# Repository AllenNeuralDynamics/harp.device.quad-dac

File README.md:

# harp.device.quad-dac
This repository contains the hardware, firmware, and software related to the Harp quad DAC

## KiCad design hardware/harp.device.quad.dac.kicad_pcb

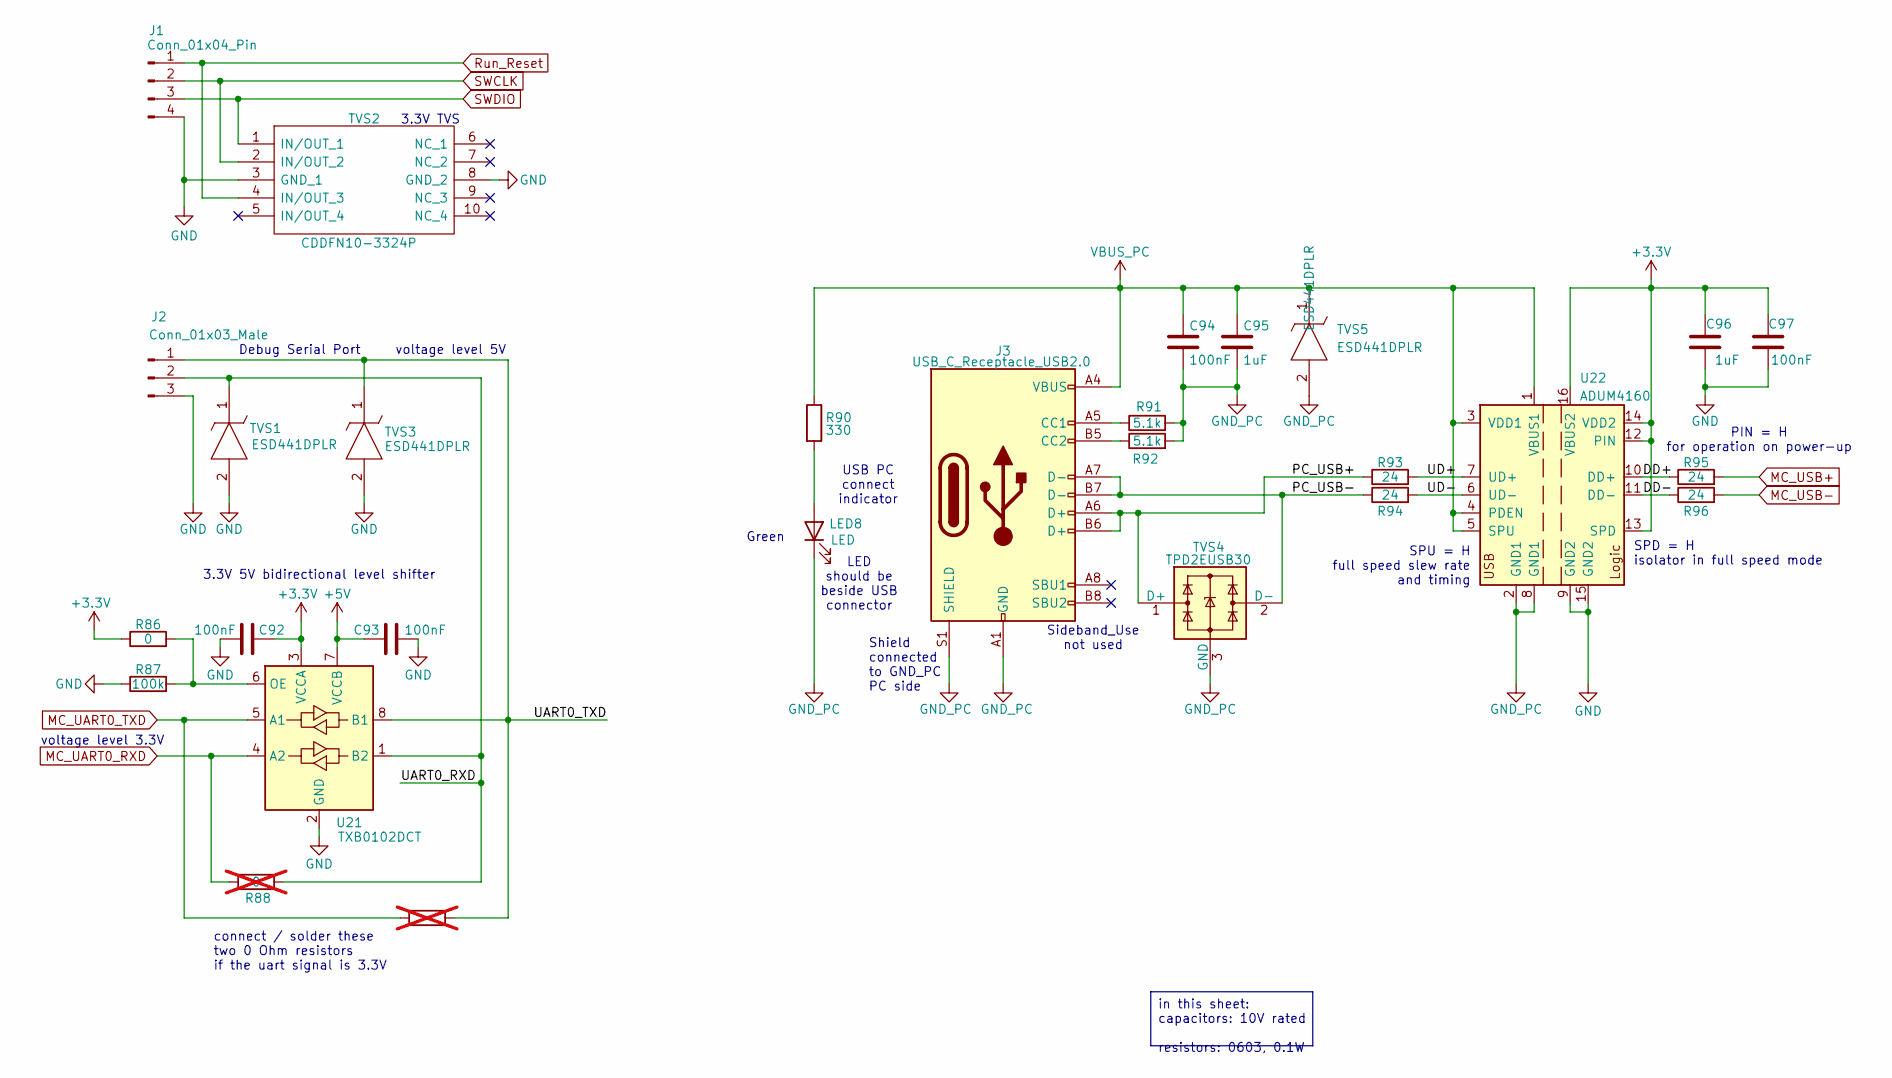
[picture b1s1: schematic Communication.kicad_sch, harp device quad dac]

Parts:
C92, C93, C94, C97: 100nF; C_0603_1608Metric; Rated Voltage 50V; Tolerance 10%; Manufacturer_Part_Number C0603C104K5RACTU
C95, C96: 1uF; C_0603_1608Metric; Rated Voltage 50V; Tolerance 10%; Manufacturer_Part_Number C1608X7R1H105K080AB
J1: Conn_01x04_Pin; PinHeader_1x04_P2.54mm_Vertical; Manufacturer_Part_Number n/a
J2: Conn_01x03_Male; PinHeader_1x03_P2.54mm_Vertical; Manufacturer_Part_Number n/a
J3: USB_C_Receptacle_USB2.0; USB_C_Receptacle_JAE_DX07S016JA1R1500; Manufacturer_Part_Number DX07S016JA1R1500
LED8: LED; LED_0603_1608Metric_Pad1.05x0.95mm_HandSolder; MPN XZCDGK53W-1VF
R86: 0; R_0603_1608Metric; MPN RC0603JR-070RL
R87: 100k; R_0603_1608Metric; Tolerance 1%; MPN RC0603FR-07100KL
R88, R89: 0; R_0603_1608Metric; MPN RC0603JR-070RL; not fitted
R90: 330; R_0603_1608Metric; Tolerance 1%; MPN RC0603FR-07330RL
R91, R92: 5.1k; R_0603_1608Metric; Tolerance 1%; MPN RC0603FR-075K1L
R93, R94, R95, R96: 24; R_0603_1608Metric; Tolerance 1%; MPN AC0603FR-0724RL
TVS1, TVS3, TVS5: ESD441DPLR; Manufacturer_Part_Number ESD441DPLR; Mouser Part Number 595-ESD441DPLR
TVS2: CDDFN10-3324P; CDDFN103324P; Manufacturer_Part_Number CDDFN10-3324P; Mouser Part Number 652-CDDFN10-3324P
TVS4: TPD2EUSB30; Texas_DRT-3
U21: TXB0102DCT; SOP50P310X90-8N
U22: ADUM4160; SOIC-16W_7.5x10.3mm_P1.27mm

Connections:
+3.3V: C92.1, C96.1, C97.2, R86.1, U21.3 (VCCA), U22.12 (PIN), U22.13 (SPD), U22.14 (VDD2), U22.16 (VBUS2); also elsewhere on the board
+5V: C93.2, U21.7 (VCCB); also elsewhere on the board
/Communication/DD+: R95.1, U22.10 (DD+)
/Communication/DD-: R96.1, U22.11 (DD-)
/Communication/PC_USB+: J3.A6 (D+), J3.B6 (D+), R93.1, TVS4.1 (D+)
/Communication/PC_USB-: J3.A7 (D-), J3.B7 (D-), R94.1, TVS4.2 (D-)
/Communication/UART0_RXD: J2.2, R88.2, TVS1.1, U21.1 (B2)
/Communication/UART0_TXD: J2.1, R89.2, TVS3.1, U21.8 (B1)
/Communication/UD+: R93.2, U22.7 (UD+)
/Communication/UD-: R94.2, U22.6 (UD-)
GND: C92.2, C93.1, C96.2, C97.1, J1.4, J2.3, R87.1, TVS1.2, TVS2.3 (GND_1), TVS2.8 (GND_2), TVS3.2, U21.2 (GND), U22.9 (GND2), U22.15 (GND2); also elsewhere on the board
GND_PC: C94.1, C95.2, J3.A1 (GND), J3.A12 (GND), J3.B1 (GND), J3.B12 (GND), J3.S1 (SHIELD), LED8.1 (K), R91.2, R92.2, TVS4.3 (GND), TVS5.2, U22.2 (GND1), U22.8 (GND1)
MC_UART0_RXD: R88.1, U21.4 (A2); also elsewhere on the board
MC_UART0_TXD: R89.1, U21.5 (A1); also elsewhere on the board
MC_USB+: R95.2; also elsewhere on the board
MC_USB-: R96.2; also elsewhere on the board
unnamed: J3.A5 (CC1), R91.1
unnamed: J3.B5 (CC2), R92.1
unnamed: LED8.2 (A), R90.2
unnamed: R86.2, R87.2, U21.6 (OE)
Run_Reset: J1.1, TVS2.4 (IN/OUT_3); also elsewhere on the board
SWCLK: J1.2, TVS2.2 (IN/OUT_2); also elsewhere on the board
SWDIO: J1.3, TVS2.1 (IN/OUT_1); also elsewhere on the board
VBUS_PC: C94.2, C95.1, J3.A4 (VBUS), J3.A9 (VBUS), J3.B4 (VBUS), J3.B9 (VBUS), R90.1, TVS5.1, U22.1 (VBUS1), U22.3 (VDD1), U22.4 (PDEN), U22.5 (SPU)

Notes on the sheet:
3.3V TVS
USB PC connect indicator
voltage level 5V
Shield connected to GND_PC PC side
LED should be beside USB connector
3.3V 5V bidirectional level shifter
connect / solder these two 0 Ohm resistors if the uart signal is 3.3V
Debug Serial Port
SPD = H isolator in full speed mode
SPU = H full speed slew rate and timing
voltage level 3.3V
Sideband_Use not used
Green
PIN = H for operation on power-up
in this sheet: capacitors: 10V rated resistors: 0603, 0.1W

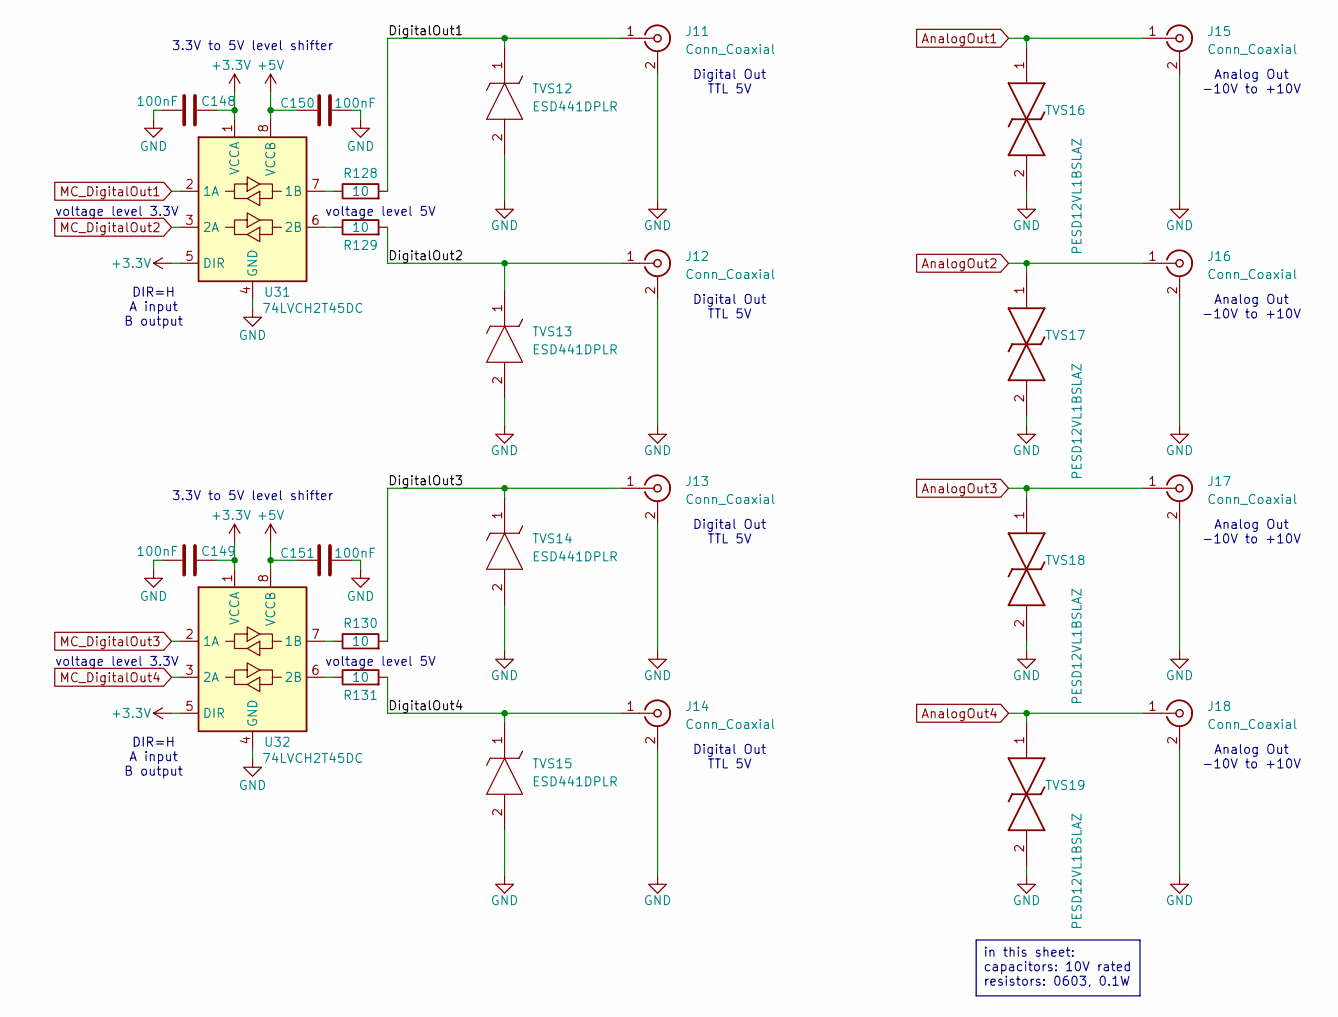
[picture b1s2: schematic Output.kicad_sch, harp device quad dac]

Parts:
C148, C149, C150, C151: 100nF; C_0603_1608Metric; Rated Voltage 50V; Tolerance 10%; Manufacturer_Part_Number C0603C104K5RACTU
J11, J12, J13, J14, J15, J16, J17, J18: Conn_Coaxial; SMA_TE_Connectivity_CONSMA002-SMD-G-T_Horizontal; MPN CONSMA002-SMD-G-T
R128, R129, R130, R131: 10; R_0603_1608Metric; Tolerance 1%; MPN AC0603FR-1310RL
TVS12, TVS13, TVS14, TVS15: ESD441DPLR; Manufacturer_Part_Number ESD441DPLR; Mouser Part Number 595-ESD441DPLR
TVS16, TVS17, TVS18, TVS19: PESD12VL1BSLAZ; Manufacturer_Part_Number PESD12VL1BSLAZ; Mouser Part Number 771-PESD12VL1BSLAZ
U31, U32: 74LVCH2T45DC; VSSOP-8_2.3x2mm_P0.5mm

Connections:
+3.3V: C148.1, C149.1, U31.1 (VCCA), U31.5 (DIR), U32.1 (VCCA), U32.5 (DIR); also elsewhere on the board
+5V: C150.2, C151.2, U31.8 (VCCB), U32.8 (VCCB); also elsewhere on the board
/Output/DigitalOut1: J11.1 (In), R128.2, TVS12.1
/Output/DigitalOut2: J12.1 (In), R129.2, TVS13.1
/Output/DigitalOut3: J13.1 (In), R130.2, TVS14.1
/Output/DigitalOut4: J14.1 (In), R131.2, TVS15.1
AnalogOut1: J15.1 (In), TVS16.1; also elsewhere on the board
AnalogOut2: J16.1 (In), TVS17.1; also elsewhere on the board
AnalogOut3: J17.1 (In), TVS18.1; also elsewhere on the board
AnalogOut4: J18.1 (In), TVS19.1; also elsewhere on the board
GND: C148.2, C149.2, C150.1, C151.1, J11.2 (Ext), J12.2 (Ext), J13.2 (Ext), J14.2 (Ext), J15.2 (Ext), J16.2 (Ext), J17.2 (Ext), J18.2 (Ext), TVS12.2, TVS13.2, TVS14.2, TVS15.2, TVS16.2, TVS17.2, TVS18.2, TVS19.2, U31.4 (GND), U32.4 (GND); also elsewhere on the board
MC_DigitalOut1: U31.2 (1A); also elsewhere on the board
MC_DigitalOut2: U31.3 (2A); also elsewhere on the board
MC_DigitalOut3: U32.2 (1A); also elsewhere on the board
MC_DigitalOut4: U32.3 (2A); also elsewhere on the board
unnamed: R128.1, U31.7 (1B)
unnamed: R129.1, U31.6 (2B)
unnamed: R130.1, U32.7 (1B)
unnamed: R131.1, U32.6 (2B)

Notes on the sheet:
voltage level 5V
Digital Out TTL 5V
Analog Out -10V to +10V
3.3V to 5V level shifter
voltage level 3.3V
DIR=H A input B output
in this sheet: capacitors: 10V rated resistors: 0603, 0.1W

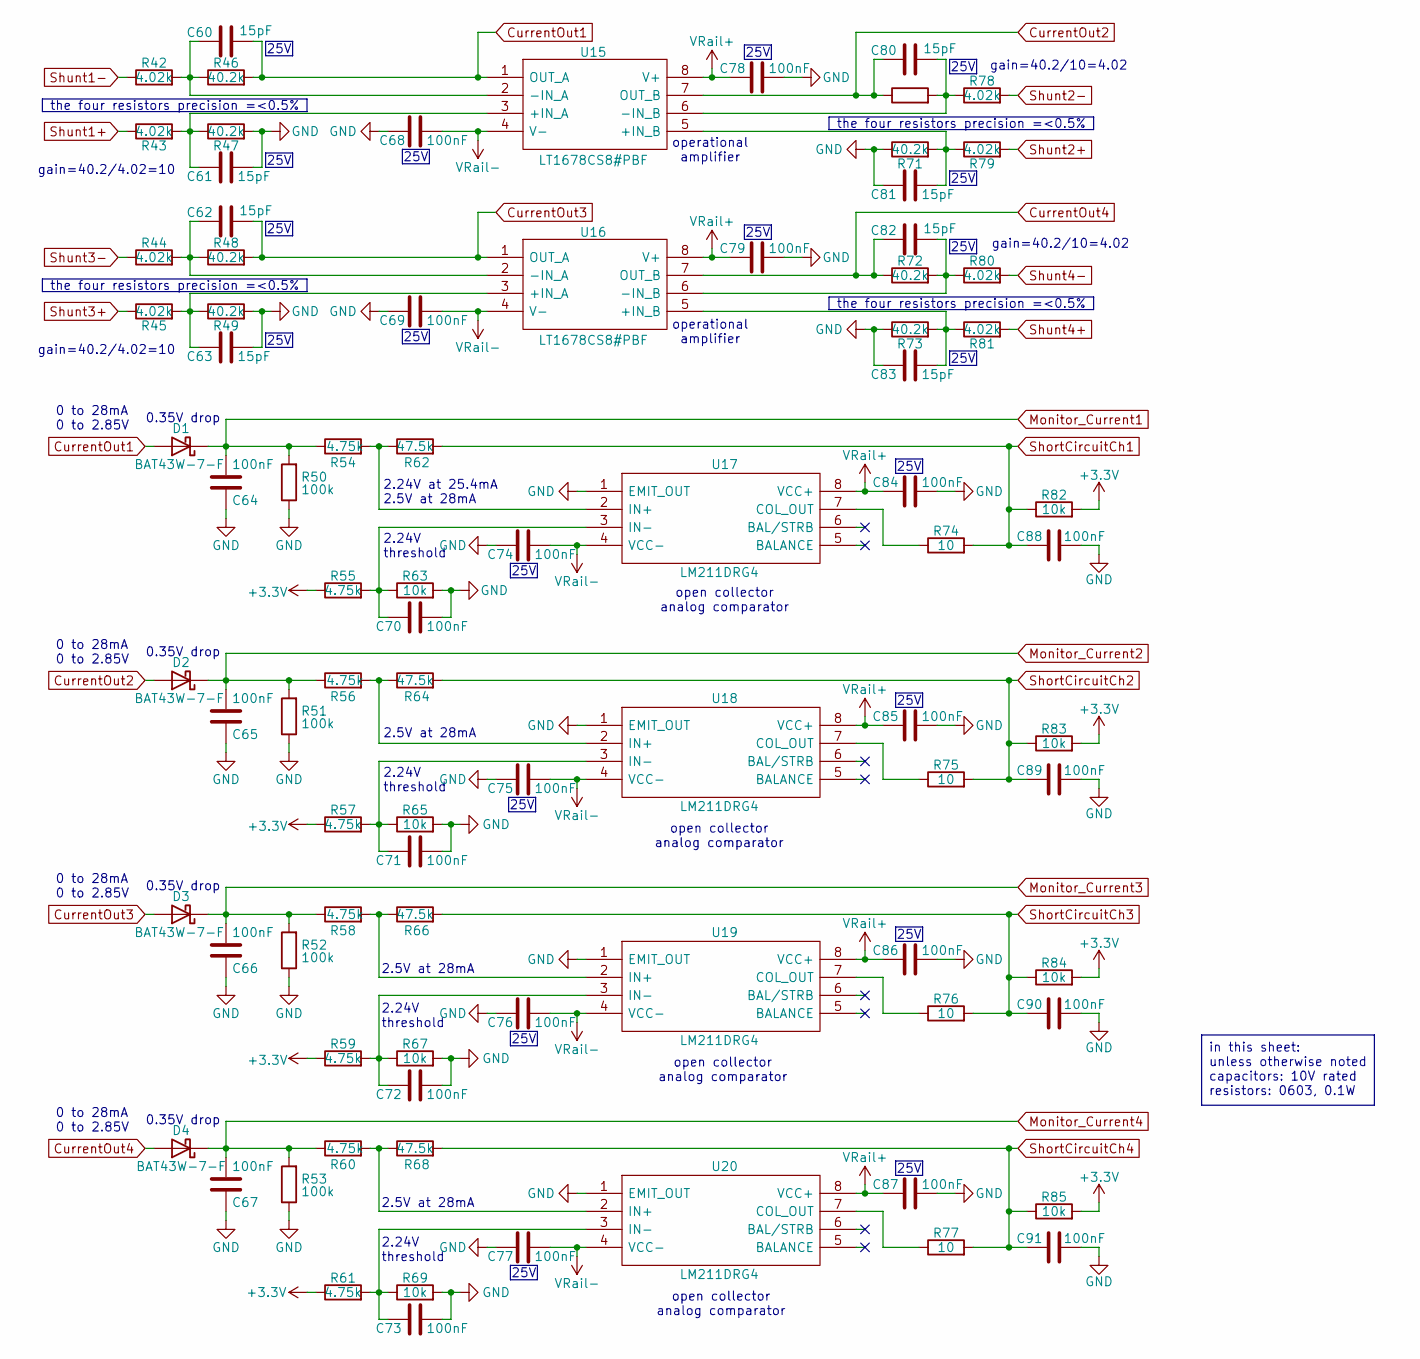
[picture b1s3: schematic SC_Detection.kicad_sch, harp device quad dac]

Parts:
C60, C61, C62, C63, C80, C81, C82, C83: 15pF; C_0603_1608Metric; Rated Voltage 50V; Tolerance 10%; Manufacturer_Part_Number C0603C150K5RACTU
C64, C65, C66, C67, C68, C69, C70, C71, C72, C73, C74, C75, C76, C77, C78, C79, C84, C85, C86, C87, C88, C89, C90, C91: 100nF; C_0603_1608Metric; Rated Voltage 50V; Tolerance 10%; Manufacturer_Part_Number C0603C104K5RACTU
D1, D2, D3, D4: BAT43W-7-F; D_SOD-123; Manufacturer_Part_Number BAT43W-7-F
R42, R43, R44, R45, R78, R79, R80, R81: 4.02k; R_0603_1608Metric; Tolerance 0.1%; MPN RT0603BRD074K02L
R46, R47, R48, R49, R70, R71, R72, R73: 40.2k; R_0603_1608Metric; Tolerance 0.1%; MPN RT0603BRD0740K2L
R50, R51, R52, R53: 100k; R_0603_1608Metric; Tolerance 1%; MPN RC0603FR-07100KL
R54, R55, R56, R57, R58, R59, R60, R61: 4.75k; R_0603_1608Metric; Tolerance 0.1%; MPN RT0603BRD074K75L
R62, R64, R66, R68: 47.5k; R_0603_1608Metric; Tolerance 0.1%; MPN RT0603BRD0747K5L
R63, R65, R67, R69, R82, R83, R84, R85: 10k; R_0603_1608Metric; Tolerance 0.1%; MPN RT0603BRD0710KL
R74, R75, R76, R77: 10; R_0603_1608Metric; Tolerance 1%; MPN AC0603FR-1310RL
U15, U16: LT1678CS8#PBF; SOIC127P599X175-8N; Manufacturer_Part_Number LT1678CS8#PBF; Mouser Part Number 584-LT1678CS8#PBF
U17, U18, U19, U20: LM211DRG4; SOIC127P600X175-8N; Manufacturer_Part_Number LM211DRG4; Mouser Part Number 595-LM211DRG4

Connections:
+3.3V: R55.1, R57.1, R59.1, R61.1, R82.2, R83.2, R84.2, R85.2; also elsewhere on the board
AnalogOut1: R42.1; also elsewhere on the board
AnalogOut2: R78.2; also elsewhere on the board
AnalogOut3: R44.1; also elsewhere on the board
AnalogOut4: R80.2; also elsewhere on the board
CurrentOut1: C60.1, D1.2 (A), R46.2, U15.1 (OUT_A)
CurrentOut2: C80.2, D2.2 (A), R70.1, U15.7 (OUT_B)
CurrentOut3: C62.1, D3.2 (A), R48.2, U16.1 (OUT_A)
CurrentOut4: C82.2, D4.2 (A), R72.1, U16.7 (OUT_B)
GND: C61.1, C63.1, C64.2, C65.2, C66.2, C67.2, C68.2, C69.2, C70.1, C71.1, C72.1, C73.1, C74.2, C75.2, C76.2, C77.2, C78.1, C79.1, C81.2, C83.2, C84.1, C85.1, C86.1, C87.1, C88.1, C89.1, C90.1, C91.1, R47.2, R49.2, R50.1, R51.1, R52.1, R53.1, R63.2, R65.2, R67.2, R69.2, R71.1, R73.1, U17.1 (EMIT_OUT), U18.1 (EMIT_OUT), U19.1 (EMIT_OUT), U20.1 (EMIT_OUT); also elsewhere on the board
Monitor_Current1: C64.1, D1.1 (K), R50.2, R54.1; also elsewhere on the board
Monitor_Current2: C65.1, D2.1 (K), R51.2, R56.1; also elsewhere on the board
Monitor_Current3: C66.1, D3.1 (K), R52.2, R58.1; also elsewhere on the board
Monitor_Current4: C67.1, D4.1 (K), R53.2, R60.1; also elsewhere on the board
unnamed: C61.2, R43.2, R47.1, U15.3 (+IN_A)
unnamed: C81.1, R71.2, R79.1, U15.5 (+IN_B)
unnamed: C60.2, R42.2, R46.1, U15.2 (-IN_A)
unnamed: C80.1, R70.2, R78.1, U15.6 (-IN_B)
unnamed: C63.2, R45.2, R49.1, U16.3 (+IN_A)
unnamed: C83.1, R73.2, R81.1, U16.5 (+IN_B)
unnamed: C62.2, R44.2, R48.1, U16.2 (-IN_A)
unnamed: C82.1, R72.2, R80.1, U16.6 (-IN_B)
unnamed: R74.1, U17.7 (COL_OUT)
unnamed: R54.2, R62.1, U17.2 (IN+)
unnamed: C70.2, R55.2, R63.1, U17.3 (IN-)
unnamed: R75.1, U18.7 (COL_OUT)
unnamed: R56.2, R64.1, U18.2 (IN+)
unnamed: C71.2, R57.2, R65.1, U18.3 (IN-)
unnamed: R76.1, U19.7 (COL_OUT)
unnamed: R58.2, R66.1, U19.2 (IN+)
unnamed: C72.2, R59.2, R67.1, U19.3 (IN-)
unnamed: R77.1, U20.7 (COL_OUT)
unnamed: R60.2, R68.1, U20.2 (IN+)
unnamed: C73.2, R61.2, R69.1, U20.3 (IN-)
ShortCircuitCh1: C88.2, R62.2, R74.2, R82.1; also elsewhere on the board
ShortCircuitCh2: C89.2, R64.2, R75.2, R83.1; also elsewhere on the board
ShortCircuitCh3: C90.2, R66.2, R76.2, R84.1; also elsewhere on the board
ShortCircuitCh4: C91.2, R68.2, R77.2, R85.1; also elsewhere on the board
Shunt1+: R43.1; also elsewhere on the board
Shunt2+: R79.2; also elsewhere on the board
Shunt3+: R45.1; also elsewhere on the board
Shunt4+: R81.2; also elsewhere on the board
VRail+: C78.2, C79.2, C84.2, C85.2, C86.2, C87.2, U15.8 (V+), U16.8 (V+), U17.8 (VCC+), U18.8 (VCC+), U19.8 (VCC+), U20.8 (VCC+); also elsewhere on the board
VRail-: C68.1, C69.1, C74.1, C75.1, C76.1, C77.1, U15.4 (V-), U16.4 (V-), U17.4 (VCC-), U18.4 (VCC-), U19.4 (VCC-), U20.4 (VCC-); also elsewhere on the board

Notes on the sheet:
0.35V drop
2.24V threshold
operational amplifier
open collector analog comparator
gain=40.2/4.02=10
gain=40.2/10=4.02
2.24V at 25.4mA
2.5V at 28mA
0 to 28mA 0 to 2.85V
25V
in this sheet: unless otherwise noted capacitors: 10V rated resistors: 0603, 0.1W
the four resistors precision =<0.5%

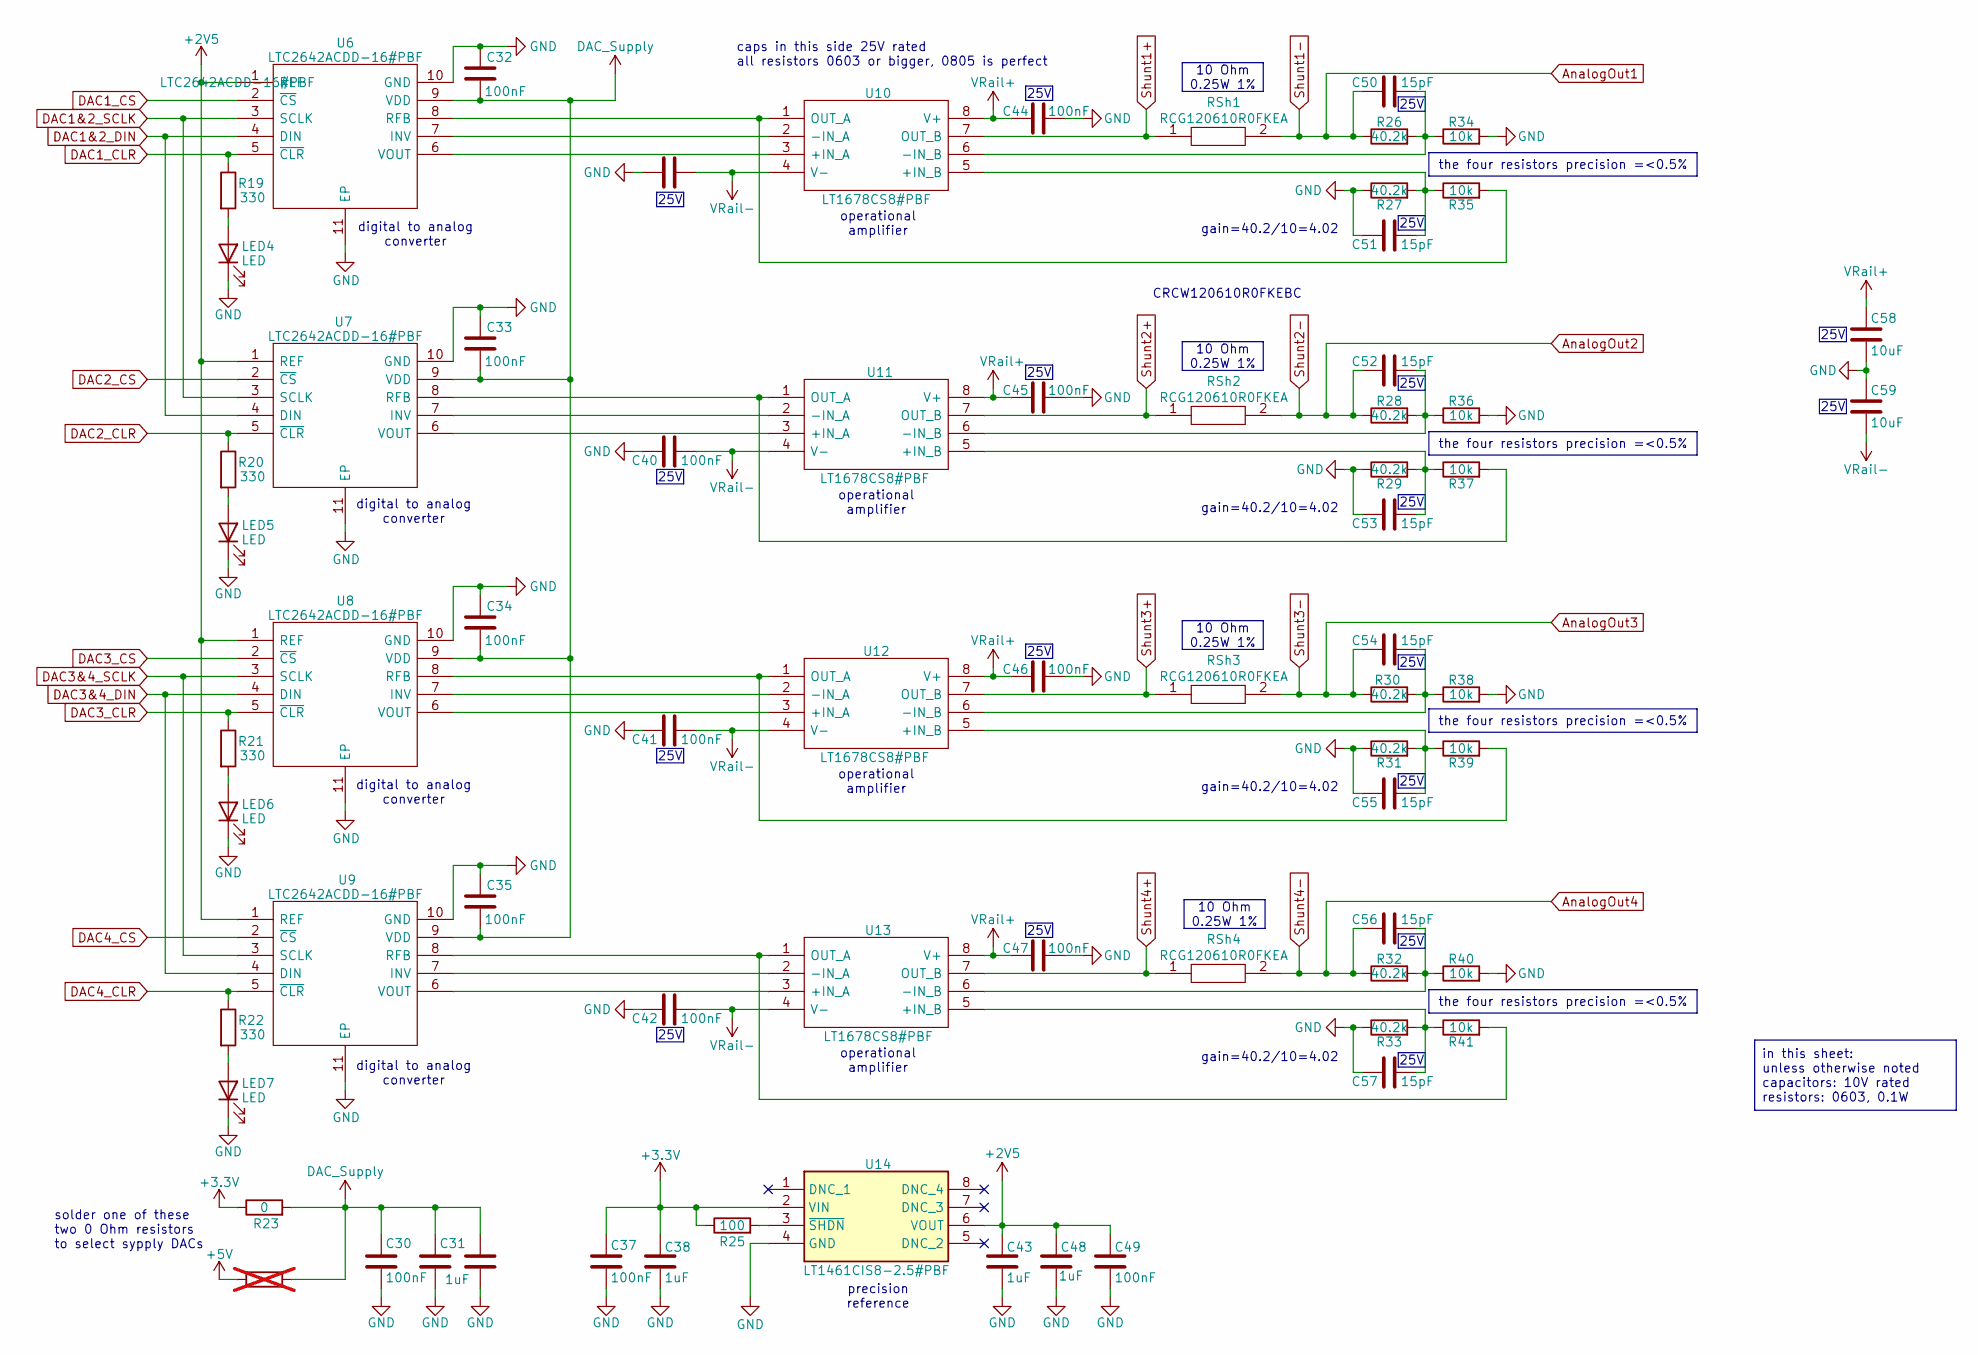
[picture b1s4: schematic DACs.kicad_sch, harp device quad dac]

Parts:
C30, C32, C33, C34, C35, C37, C39, C40, C41, C42, C44, C45, C46, C47, C49: 100nF; C_0603_1608Metric; Rated Voltage 50V; Tolerance 10%; Manufacturer_Part_Number C0603C104K5RACTU
C31, C38, C43, C48: 1uF; C_0603_1608Metric; Rated Voltage 50V; Tolerance 10%; Manufacturer_Part_Number C1608X7R1H105K080AB
C36, C58, C59: 10uF; C_0603_1608Metric; Rated Voltage 25V; Tolerance 10%; Manufacturer_Part_Number GRM188R61E106KA73D
C50, C51, C52, C53, C54, C55, C56, C57: 15pF; C_0603_1608Metric; Rated Voltage 50V; Tolerance 10%; Manufacturer_Part_Number C0603C150K5RACTU
LED4, LED5, LED6, LED7: LED; LED_0603_1608Metric_Pad1.05x0.95mm_HandSolder; MPN XZCDGK53W-1VF
R19, R20, R21, R22: 330; R_0603_1608Metric; Tolerance 1%; MPN RC0603FR-07330RL
R23: 0; R_0603_1608Metric; MPN RC0603JR-070RL
R24: 0; R_0603_1608Metric; MPN RC0603JR-070RL; not fitted
R25: 100; R_0603_1608Metric; Tolerance 1%; MPN AC0603FR-13100RL
R26, R27, R28, R29, R30, R31, R32, R33: 40.2k; R_0603_1608Metric; Tolerance 0.1%; MPN RT0603BRD0740K2L
R34, R35, R36, R37, R38, R39, R40, R41: 10k; R_0603_1608Metric; Tolerance 0.1%; MPN RT0603BRD0710KL
RSh1, RSh2, RSh3, RSh4: RCG120610R0FKEA; R_1206_3216Metric; Tolerance 1%; Manufacturer_Part_Number CRCW120610R0FKEBC; Mouser Part Number 71-CRCW120610R0FKEBC
U6, U7, U8, U9: LTC2642ACDD-16#PBF; SON50P300X300X80-11N-D; Manufacturer_Part_Number LTC2642ACDD-16#PBF; Mouser Part Number 584-C2642ACDD-16PBF
U10, U11, U12, U13: LT1678CS8#PBF; SOIC127P599X175-8N; Manufacturer_Part_Number LT1678CS8#PBF; Mouser Part Number 584-LT1678CS8#PBF
U14: LT1461CIS8-2.5#PBF; SOIC127P599X175-8N; Manufacturer_Part_Number LT1461CIS8-2.5#PBF; Mouser Part Number 584-1461CIS8-2.5PBF

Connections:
+2V5: C43.1, C48.1, C49.2, U6.1 (REF), U7.1 (REF), U8.1 (REF), U9.1 (REF), U14.6 (VOUT)
+3.3V: C37.2, C38.1, R23.1, R25.1, U14.2 (VIN); also elsewhere on the board
+5V: R24.1; also elsewhere on the board
AnalogOut1: C50.2, R26.1, RSh1.2; also elsewhere on the board
AnalogOut2: C52.2, R28.1, RSh2.2; also elsewhere on the board
AnalogOut3: C54.2, R30.1, RSh3.2; also elsewhere on the board
AnalogOut4: C56.2, R32.1, RSh4.2; also elsewhere on the board
DAC1&2_DIN: U6.4 (DIN), U7.4 (DIN); also elsewhere on the board
DAC1&2_SCLK: U6.3 (SCLK), U7.3 (SCLK); also elsewhere on the board
DAC1_CLR: R19.1, U6.5 (~CLR); also elsewhere on the board
DAC1_CS: U6.2 (~CS); also elsewhere on the board
DAC2_CLR: R20.1, U7.5 (~CLR); also elsewhere on the board
DAC2_CS: U7.2 (~CS); also elsewhere on the board
DAC3&4_DIN: U8.4 (DIN), U9.4 (DIN); also elsewhere on the board
DAC3&4_SCLK: U8.3 (SCLK), U9.3 (SCLK); also elsewhere on the board
DAC3_CLR: R21.1, U8.5 (~CLR); also elsewhere on the board
DAC3_CS: U8.2 (~CS); also elsewhere on the board
DAC4_CLR: R22.1, U9.5 (~CLR); also elsewhere on the board
DAC4_CS: U9.2 (~CS); also elsewhere on the board
DAC_Supply: C30.2, C31.1, C32.1, C33.1, C34.1, C35.1, C36.1, R23.2, R24.2, U6.9 (VDD), U7.9 (VDD), U8.9 (VDD), U9.9 (VDD)
GND: C30.1, C31.2, C32.2, C33.2, C34.2, C35.2, C36.2, C37.1, C38.2, C39.2, C40.2, C41.2, C42.2, C43.2, C44.1, C45.1, C46.1, C47.1, C48.2, C49.1, C51.2, C53.2, C55.2, C57.2, C58.2, C59.1, LED4.1 (K), LED5.1 (K), LED6.1 (K), LED7.1 (K), R27.1, R29.1, R31.1, R33.1, R34.2, R36.2, R38.2, R40.2, U6.10 (GND), U6.11 (EP), U7.10 (GND), U7.11 (EP), U8.10 (GND), U8.11 (EP), U9.10 (GND), U9.11 (EP), U14.4 (GND); also elsewhere on the board
unnamed: LED4.2 (A), R19.2
unnamed: LED5.2 (A), R20.2
unnamed: LED6.2 (A), R21.2
unnamed: LED7.2 (A), R22.2
unnamed: U6.6 (VOUT), U10.3 (+IN_A)
unnamed: C51.1, R27.2, R35.1, U10.5 (+IN_B)
unnamed: U6.7 (INV), U10.2 (-IN_A)
unnamed: C50.1, R26.2, R34.1, U10.6 (-IN_B)
unnamed: R35.2, U6.8 (RFB), U10.1 (OUT_A)
unnamed: U7.6 (VOUT), U11.3 (+IN_A)
unnamed: C53.1, R29.2, R37.1, U11.5 (+IN_B)
unnamed: U7.7 (INV), U11.2 (-IN_A)
unnamed: C52.1, R28.2, R36.1, U11.6 (-IN_B)
unnamed: R37.2, U7.8 (RFB), U11.1 (OUT_A)
unnamed: U8.6 (VOUT), U12.3 (+IN_A)
unnamed: C55.1, R31.2, R39.1, U12.5 (+IN_B)
unnamed: U8.7 (INV), U12.2 (-IN_A)
unnamed: C54.1, R30.2, R38.1, U12.6 (-IN_B)
unnamed: R39.2, U8.8 (RFB), U12.1 (OUT_A)
unnamed: U9.6 (VOUT), U13.3 (+IN_A)
unnamed: C57.1, R33.2, R41.1, U13.5 (+IN_B)
unnamed: U9.7 (INV), U13.2 (-IN_A)
unnamed: C56.1, R32.2, R40.1, U13.6 (-IN_B)
unnamed: R41.2, U9.8 (RFB), U13.1 (OUT_A)
unnamed: R25.2, U14.3 (~SHDN)
Shunt1+: RSh1.1, U10.7 (OUT_B); also elsewhere on the board
Shunt2+: RSh2.1, U11.7 (OUT_B); also elsewhere on the board
Shunt3+: RSh3.1, U12.7 (OUT_B); also elsewhere on the board
Shunt4+: RSh4.1, U13.7 (OUT_B); also elsewhere on the board
VRail+: C44.2, C45.2, C46.2, C47.2, C58.1, U10.8 (V+), U11.8 (V+), U12.8 (V+), U13.8 (V+); also elsewhere on the board
VRail-: C39.1, C40.1, C41.1, C42.1, C59.2, U10.4 (V-), U11.4 (V-), U12.4 (V-), U13.4 (V-); also elsewhere on the board

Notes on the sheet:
digital to analog converter
operational amplifier
precision reference
gain=40.2/10=4.02
CRCW120610R0FKEBC
caps in this side 25V rated all resistors 0603 or bigger, 0805 is perfect
solder one of these two 0 Ohm resistors to select sypply DACs
10 Ohm 0.25W 1%
in this sheet: unless otherwise noted capacitors: 10V rated resistors: 0603, 0.1W
25V
the four resistors precision =<0.5%
